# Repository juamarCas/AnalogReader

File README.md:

# Analog Reader
Circuit board based on STM303RBT6 microcontroller, made using Kicad v6

## Footage

## Other parts of the project
* [MQTT Middleware](https://github.com/juamarCas/MQTT_middleware)
* [API REST](https://github.com/juamarCas/Sensor_API_REST)

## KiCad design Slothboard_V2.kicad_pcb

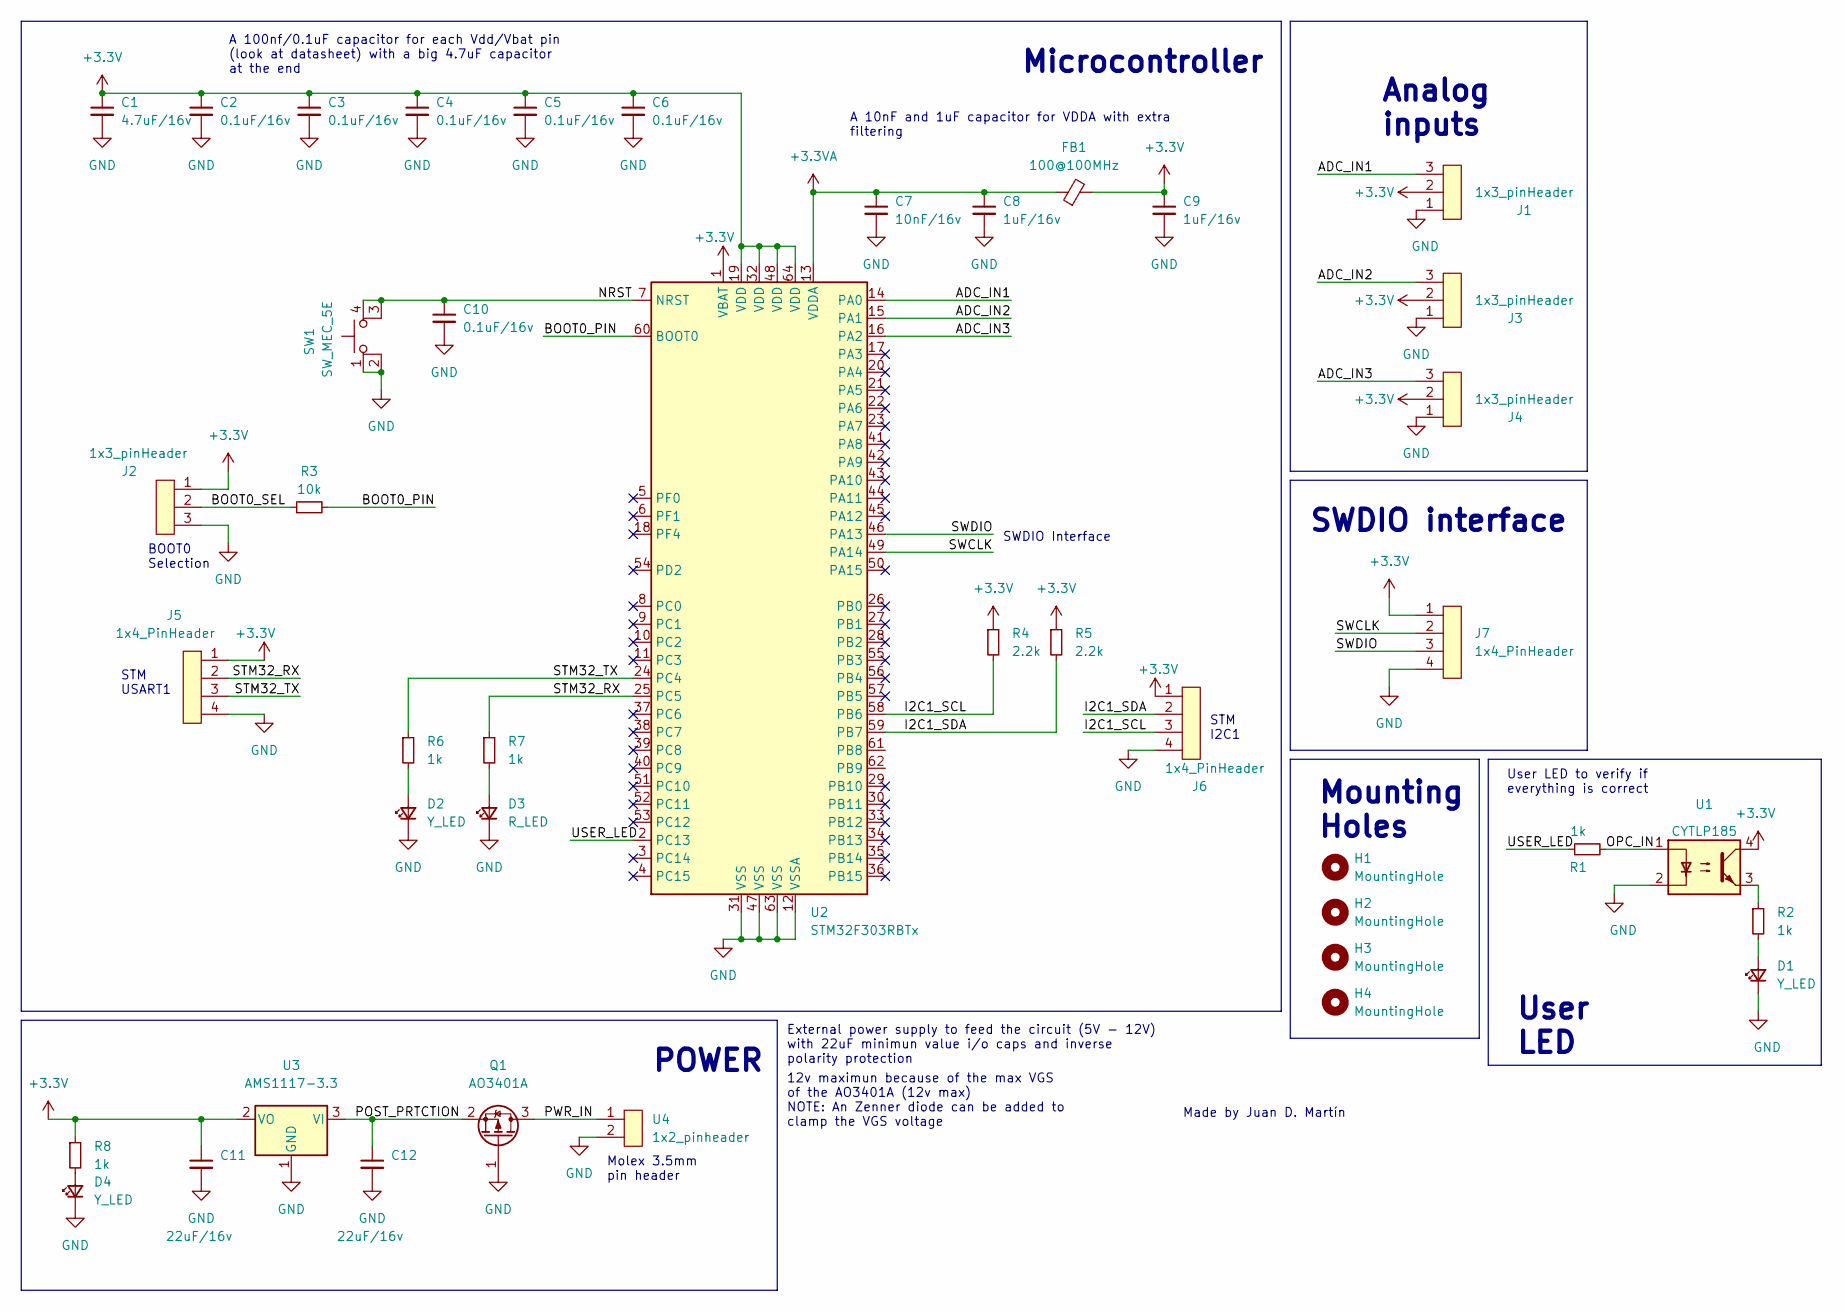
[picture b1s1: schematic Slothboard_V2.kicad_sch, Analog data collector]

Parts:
C1: 4.7uF/16v; 0603_Capacitor; LCSC Part # C19666
C2, C3, C4, C5, C6, C10: 0.1uF/16v; 0603_Capacitor; LCSC Part # C14663
C7: 10nF/16v; 0603_Capacitor; LCSC Part # C57112
C8, C9: 1uF/16v; 0603_Capacitor; JLCPCB Part # C15849
C11, C12: 22uF/16v; 0805_Capacitor; JLCPCB Part # C129303
D1, D2, D4: Y_LED; LED_0805; JLCPCB Part # C2296
D3: R_LED; LED_0805; JLCPCB Part # C84256
FB1: 100@100MHz; 0805_Resistor; JLCPCB Part # C1015
H1, H2, H3, H4: MountingHole; MountingHole_2.2mm_M2
J1, J2, J3, J4: 1x3_pinHeader; PinHeader_1x03_P2.54mm_Vertical
J5, J6: 1x4_PinHeader; PinHeader_1x04_P2.54mm_Horizontal
J7: 1x4_PinHeader; PinHeader_1x04_P2.54mm_Vertical
Q1: AO3401A; SOT-23; JLCPCB Part # C15127
R1, R2, R6, R7, R8: 1k; 0805_Resistor; JLCPCB Part # C17513
R3: 10k; 0805_Resistor; JLCPCB Part # C17414
R4, R5: 2.2k; 0805_Resistor; JLCPCB Part # C17520
SW1: SW_MEC_5E; PUSH_6x6mm_SMD
U1: CYTLP185; SOIC-4; JLCPCB Part # C385052
U2: STM32F303RBTx; LQFP-64_10x10mm_P0.5mm; JLCPCB Part # C130453
U3: AMS1117-3.3; SOT-223-3_TabPin2; JLCPCB Part # C6186
U4: 1x2_pinheader; Molex_KK-396_A-41791-0002_1x02_P3.96mm_Vertical

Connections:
+3.3VA: C7.1, C8.1, FB1.1, U2.13 (VDDA)
+3V3: C1.1, C2.1, C3.1, C4.1, C5.1, C6.1, C9.1, C11.1, FB1.2, J1.2, J2.1, J3.2, J4.2, J5.1, J6.1, J7.1, R4.1, R5.1, R8.1, U1.4, U2.1 (VBAT), U2.19 (VDD), U2.32 (VDD), U2.48 (VDD), U2.64 (VDD), U3.2 (VO)
/ADC_IN1: J1.3, U2.14 (PA0)
/ADC_IN2: J3.3, U2.15 (PA1)
/ADC_IN3: J4.3, U2.16 (PA2)
/BOOT0_PIN: R3.2, U2.60 (BOOT0)
/BOOT0_SEL: J2.2, R3.1
/I2C1_SCL: J6.3, R4.2, U2.58 (PB6)
/I2C1_SDA: J6.2, R5.2, U2.59 (PB7)
/NRST: C10.1, SW1.3 (K), SW1.4 (A), U2.7 (NRST)
/OPC_IN: R1.2, U1.1
/POST_PRTCTION: C12.1, Q1.2 (S), U3.3 (VI)
/PWR_IN: Q1.3 (D), U4.1
/STM32_RX: J5.2, R7.1, U2.25 (PC5)
/STM32_TX: J5.3, R6.1, U2.24 (PC4)
/SWCLK: J7.2, U2.49 (PA14)
/SWDIO: J7.3, U2.46 (PA13)
/USER_LED: R1.1, U2.2 (PC13)
GND: C1.2, C2.2, C3.2, C4.2, C5.2, C6.2, C7.2, C8.2, C9.2, C10.2, C11.2, C12.2, D1.1 (K), D2.1 (K), D3.1 (K), D4.1 (K), J1.1, J2.3, J3.1, J4.1, J5.4, J6.4, J7.4, Q1.1 (G), SW1.1, SW1.2, U1.2, U2.12 (VSSA), U2.31 (VSS), U2.47 (VSS), U2.63 (VSS), U3.1 (GND), U4.2
unnamed: D1.2 (A), R2.2
unnamed: D2.2 (A), R6.2
unnamed: D3.2 (A), R7.2
unnamed: D4.2 (A), R8.2
unnamed: R2.1, U1.3

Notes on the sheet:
User LED
Molex 3.5mm pin header
A 10nF and 1uF capacitor for VDDA with extra filtering
A 100nf/0.1uF capacitor for each Vdd/Vbat pin (look at datasheet) with a big 4.7uF capacitor at the end
STM USART1
BOOT0 Selection
POWER
Mounting Holes
SWDIO interface
External power supply to feed the circuit (5V - 12V) with 22uF minimun value i/o caps and inverse polarity protection
SWDIO Interface
12v maximun because of the max VGS of the AO3401A (12v max) NOTE: An Zenner diode can be added to clamp the VGS voltage
User LED to verify if everything is correct
Microcontroller
STM I2C1
Made by Juan D. Martín
Analog inputs

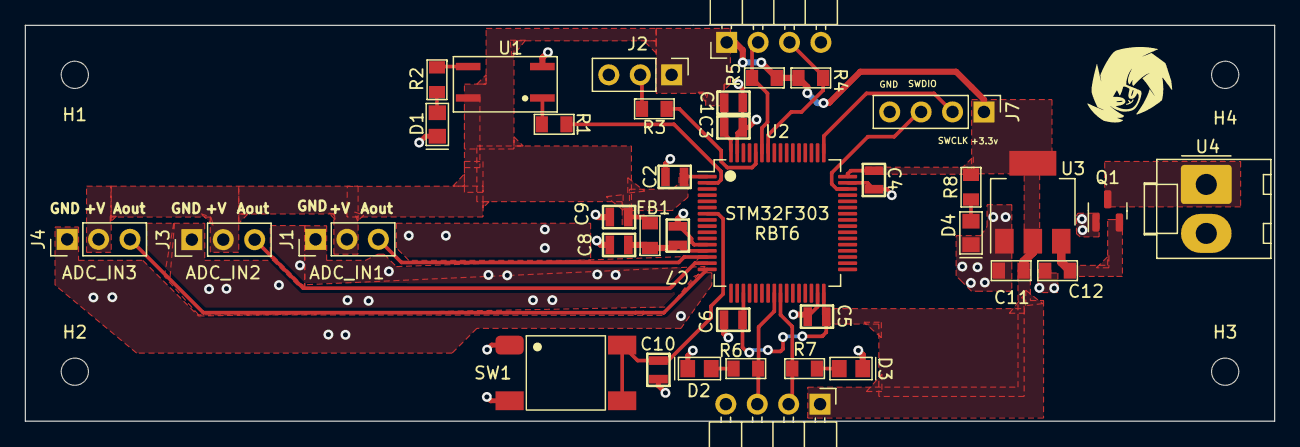
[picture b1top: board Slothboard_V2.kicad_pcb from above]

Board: 2 copper layers, 101.0 x 32.0 mm, 42 parts (0 on the bottom side), 24 nets.

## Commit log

2022-10-10 finished 0.1v
2022-10-10 add images
2022-11-01 added more photos
2022-11-15 added photo
